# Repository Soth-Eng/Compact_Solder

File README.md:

# Compact_Solder
JBC Compact Soldering Station

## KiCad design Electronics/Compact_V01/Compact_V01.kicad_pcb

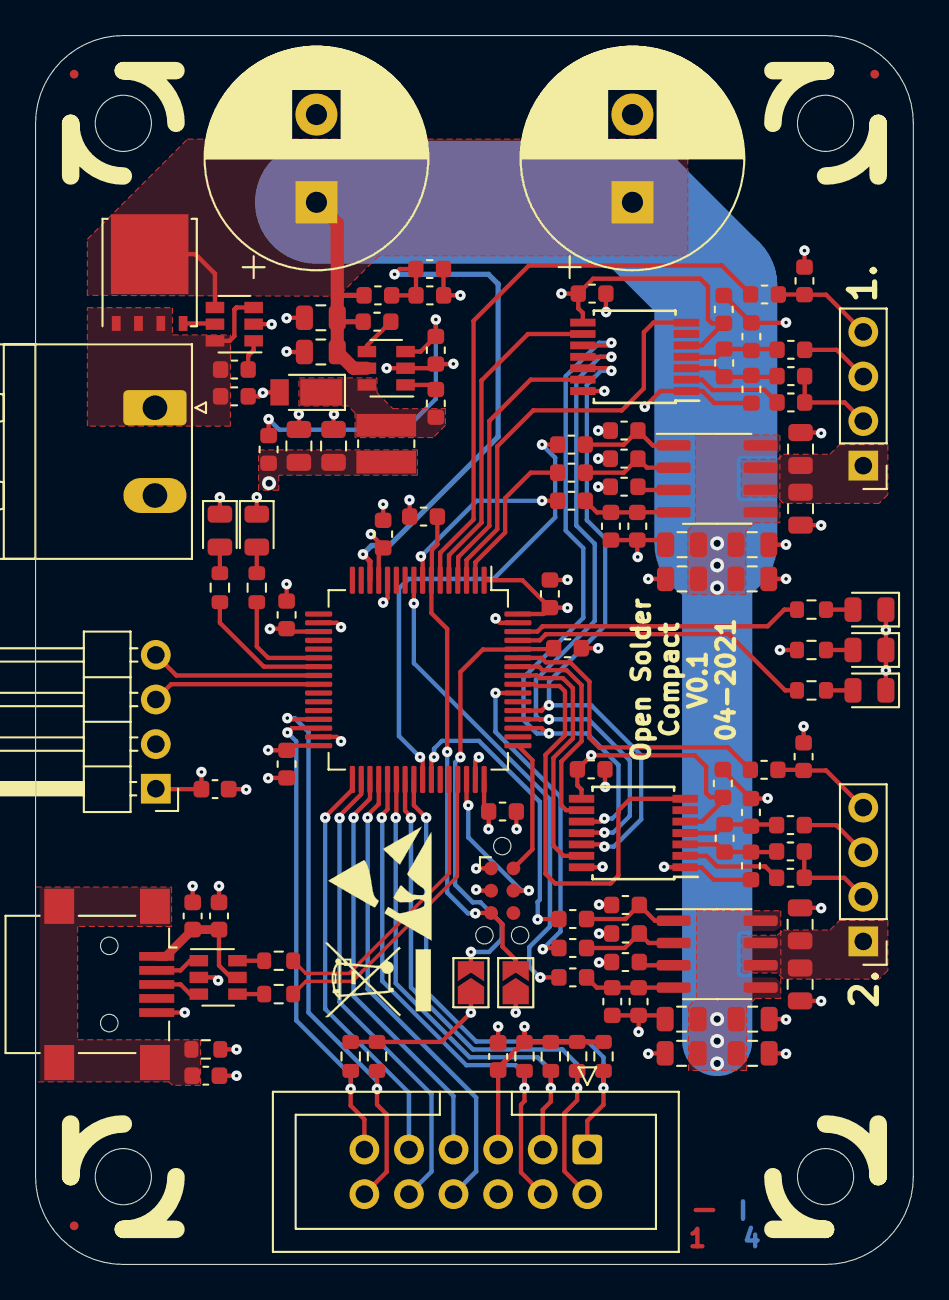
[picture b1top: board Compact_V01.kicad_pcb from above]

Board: 4 copper layers, 50.0 x 70.0 mm, 121 parts (0 on the bottom side), 81 nets.

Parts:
C1, C2, C3, C4, C13, C16, C20, C22, C23, C24, C31: 10nF; C_0603_1608Metric
C5, C6, C19, C21, C33, C34, C35, C56, C59, C60, C61, C62, C63, C64: 100nF; C_0603_1608Metric
C7, C8, C9, C10, C11, C12, C14, C15, C25, C26, C27, C28, C29, C30: 2.2uF; C_0805_2012Metric
C17, C18: 4.7uF; C_0805_2012Metric
C32: 1U; C_0603_1608Metric
C55: 22nF; C_0603_1608Metric
C57, C58: 1000uF; CP_Radial_D12.5mm_P5.00mm
D1: DFLS; D_PowerDI-123
D2, D3: GRN; LED_0805_2012Metric
D4: RED; LED_0805_2012Metric
D5, D6: BLUE; LED_0805_2012Metric
FID1, FID2, FID3: Fiducial; Fiducial_0.5mm_Mask1mm
H1, H2, H3, H4: MountingHole; MountingHole_3.2mm_M3_DIN965
J1, J2: IRON; PinHeader_1x04_P2.54mm_Vertical
J3: USB_B_Mini; USB_Mini-B_Lumberg_2486_01_Horizontal
J4: HMI; IDC-Header_2x06_P2.54mm_Vertical
J5: Power; PhoenixContact_MSTBA_2,5_2-G_1x02_P5.00mm_Horizontal
J6: PROG; Tag-Connect_TC2030-IDC-NL_2x03_P1.27mm_Vertical
J7: EXT; PinHeader_1x04_P2.54mm_Horizontal
JP1: RESET; SolderJumper-2_P1.3mm_Open_TrianglePad1.0x1.5mm
JP2: BOOT; SolderJumper-2_P1.3mm_Open_TrianglePad1.0x1.5mm
L1: 15uH; L_Wuerth_MAPI-3015
Q1: BSC028N06LS3; TDSON-8-1
R1, R7, R8, R17, R20, R27, R28: 10K; R_0603_1608Metric
R2: 1M; R_0603_1608Metric
R3, R4, R5, R23, R24, R25: 330E; R_0603_1608Metric
R6, R21: 22E; R_0603_1608Metric
R9, R10, R22, R26, R29, R30, R36, R37, R40, R41, R42, R43, R44: 1K; R_0603_1608Metric
R11, R31: 225E; R_0603_1608Metric
R12, R32: 0E; R_0603_1608Metric
R13, R14, R15, R33, R34, R35: 2K; R_0603_1608Metric
R16, R18: 100K; R_0603_1608Metric
R19: 33K; R_0603_1608Metric
R38, R39: 5.6K; R_0603_1608Metric
U1, U4: MAX31856; TSSOP-14_4.4x5mm_P0.65mm
U2, U5: NCV84140; SOIC-8_3.9x4.9mm_P1.27mm
U3: LMR16006YQ; SOT-23-6
U6: WE-TVS-82400102; SOT-23-6
U10: LM74700; SOT-23-6
U11: STM32L433RCTx; LQFP-64_10x10mm_P0.5mm

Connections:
+3V3: C5.1, C6.1, C17.1, C18.1, C19.1, C21.1, C34.1, C35.1, C60.1, C61.1, C62.1, C63.1, C64.1, J4.5, J6.1, J7.1, JP2.1, L1.2, R10.1, R19.1, R22.1, R26.1, R30.1, R36.1, R37.1, R38.1, R39.1, R40.1, U1.5, U1.8, U4.5, U4.8, U11.1, U11.13, U11.19, U11.32, U11.48, U11.64
+5V: C32.1, C33.1, J3.1, U6.5
/CS_1: R5.2, U11.8
/CS_2: R25.2, U11.9
/CS_EN_1: R4.2, U11.2
/CS_EN_2: R24.2, U11.55
/DRDY_1: U1.7, U11.3
/DRDY_2: U4.7, U11.56
/Detect_1: R9.2, U11.6
/Detect_2: R29.2, U11.59
/FAULT_1: U1.13, U11.4
/FAULT_2: U4.13, U11.57
/Front-End/HEATER: C7.1, C9.1, J1.1, U2.6, U2.7
/Front-End/Probe: J1.4, R9.1, R10.2
/Front-End/TC+: J1.3, R13.1
/MCU/BOOT0: JP2.2, R1.1, U11.60
/MCU/ERR: R42.1, U11.22
/MCU/H1_STAT: R43.1, U11.62
/MCU/H2_STAT: R44.1, U11.61
/MCU/I2C_SCL: J4.12, R39.2, U11.29
/MCU/I2C_SDA: J4.11, R38.2, U11.30
/MCU/IO_1: J4.1, R22.2, U11.40
/MCU/IO_2: J4.2, R26.2, U11.39
/MCU/IO_3: J4.3, R36.2, U11.38
/MCU/IO_4: J4.4, R37.2, U11.37
/MCU/NRST: C59.1, J6.5, JP1.2, U11.7
/MCU/RXD: J7.3, U11.25
/MCU/SPI_MISO: J4.7, U11.35
/MCU/SPI_MOSI: J4.8, U11.36
/MCU/SPI_NSS: J4.9, U11.33
/MCU/SPI_SCK: J4.10, U11.34
/MCU/STAT: R41.1, U11.23
/MCU/SWCLK: J6.2, U11.49
/MCU/SWDIO: J6.4, U11.46
/MCU/TXD: J7.4, U11.24
/MCU/USB_D+: R6.1, U11.45
/MCU/USB_D-: R21.1, U11.44
/PWM_IN_1: R3.2, U11.41
/PWM_IN_2: R23.2, U11.42
/SCK: U1.10, U4.10, U11.51
/SDI: U1.12, U4.12, U11.53
/SDO: U1.11, U4.11, U11.52
/SS_1: U1.9, U11.5
/SS_2: U4.9, U11.58
/VBUS_M: C13.1, R16.2, R17.1, U11.14
/sheet6064770F/HEATER: C25.1, C27.1, J2.1, U5.6, U5.7
/sheet6064770F/Probe: J2.4, R29.1, R30.2
/sheet6064770F/TC+: J2.3, R33.1
GND: C1.2, C2.1, C4.2, C5.2, C6.2, C7.2, C8.2, C9.2, C10.2, C11.2, C12.2, C13.2, C14.2, C15.2, C17.2, C18.2, C19.2, C20.2, C21.2, C22.1, C24.2, C25.2, C26.2, C27.2, C28.2, C29.2, C30.2, C31.2, C32.2, C33.2, C34.2, C35.2, C55.2, C57.2, C58.2, C59.2, C60.2, C61.2, C62.2, C63.2, C64.2, D1.2, D2.1, D3.1, D4.1, D5.1, D6.1, J1.2, J2.2, J3.5, J4.6, J5.2, J6.3, J7.2, JP1.1, R1.2, R2.2, R7.2, R8.2, R11.2, R12.2, R14.1, R15.1, R17.2, R20.2, R27.2, R28.2, R31.2, R32.2, R34.1, R35.1, U1.1, U1.14, U3.2, U4.1, U4.14, U6.2, U10.2, U11.12, U11.18, U11.31, U11.47, U11.63
unnamed: C1.1, R5.1, R11.1, U2.4
unnamed: C2.2, C3.1, R13.2, U1.4
unnamed: C3.2, C4.1, R14.2, U1.3
unnamed: C16.1, U3.1
unnamed: C16.2, D1.1, L1.1, U3.6
unnamed: C20.1, R25.1, R31.1, U5.4
unnamed: C22.2, C23.1, R33.2, U4.4
unnamed: C23.2, C24.1, R34.2, U4.3
unnamed: C31.1, J3.6, R2.1
unnamed: C55.1, C56.1, J5.1, Q1.1, Q1.2, Q1.3, U10.3, U10.6
unnamed: C56.2, U10.1
unnamed: D2.2, R40.2
unnamed: D3.2, R41.2
unnamed: D4.2, R42.2
unnamed: D5.2, R43.2
unnamed: D6.2, R44.2
unnamed: J3.2, U6.1
unnamed: J3.3, U6.3
unnamed: Q1.4, U10.5
unnamed: R3.1, R7.1, U2.1
unnamed: R4.1, R8.1, U2.2
unnamed: R6.2, U6.4
unnamed: R12.1, U2.3
unnamed: R15.2, U1.2
unnamed: R18.2, U3.4
unnamed: R19.2, R20.1, U3.3
unnamed: R21.2, U6.6
unnamed: R23.1, R27.1, U5.1
unnamed: R24.1, R28.1, U5.2
unnamed: R32.1, U5.3
unnamed: R35.2, U4.2
VBUS: C8.1, C10.1, C11.1, C12.1, C14.1, C15.1, C26.1, C28.1, C29.1, C30.1, C57.1, C58.1, Q1.5, R16.1, R18.1, U2.5, U2.8, U3.5, U5.5, U5.8, U10.4

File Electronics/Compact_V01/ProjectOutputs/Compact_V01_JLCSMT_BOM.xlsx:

Comment | Designator | Footprint
WEEE-Logo_4.2x6mm_SilkScreen | REF** | WEEE-Logo_4.2x6mm_SilkScreen
ESD-Logo_6.6x6mm_SilkScreen | REF** | ESD-Logo_6.6x6mm_SilkScreen
1K | R44,R43,R42,R41,R40,R37,R36,R26,R22,R30,R29,R10,R9 | R_0603_1608Metric
BLUE | D6,D5 | LED_0805_2012Metric
RED | D4 | LED_0805_2012Metric
GRN | D3,D2 | LED_0805_2012Metric
EXT | J7 | PinHeader_1x04_P2.54mm_Horizontal
100nF | C35,C34,C33,C64,C63,C62,C61,C60,C59,C56,C21,C19,C6,C5 | C_0603_1608Metric
BOOT | JP2 | SolderJumper-2_P1.3mm_Open_TrianglePad1.0x1.5mm
RESET | JP1 | SolderJumper-2_P1.3mm_Open_TrianglePad1.0x1.5mm
PROG | J6 | Tag-Connect_TC2030-IDC-NL_2x03_P1.27mm_Vertical
5.6K | R39,R38 | R_0603_1608Metric
HMI | J4 | IDC-Header_2x06_P2.54mm_Vertical
WE-TVS-82400102 | U6 | SOT-23-6
22E | R21,R6 | R_0603_1608Metric
1M | R2 | R_0603_1608Metric
1U | C32 | C_0603_1608Metric
10nF | C31,C24,C23,C22,C20,C16,C13,C4,C3,C2,C1 | C_0603_1608Metric
USB_B_Mini | J3 | USB_Mini-B_Lumberg_2486_01_Horizontal
IRON | J2,J1 | PinHeader_1x04_P2.54mm_Vertical
Power | J5 | PhoenixContact_MSTBA_2,5_2-G_1x02_P5.00mm_Horizontal
STM32L433RCTx | U11 | LQFP-64_10x10mm_P0.5mm
10K | R1,R28,R27,R20,R17,R8,R7 | R_0603_1608Metric
1000uF | C58,C57 | CP_Radial_D12.5mm_P5.00mm
LM74700 | U10 | SOT-23-6
BSC028N06LS3 | Q1 | TDSON-8-1
22nF | C55 | C_0603_1608Metric
NCV84140 | U5,U2 | SOIC-8_3.9x4.9mm_P1.27mm
MAX31856 | U4,U1 | TSSOP-14_4.4x5mm_P0.65mm
2K | R35,R34,R33,R15,R14,R13 | R_0603_1608Metric
0E | R32,R12 | R_0603_1608Metric
225E | R31,R11 | R_0603_1608Metric
330E | R25,R24,R23,R5,R4,R3 | R_0603_1608Metric
2.2uF | C30,C29,C28,C27,C26,C25,C15,C14,C12,C11,C10,C9,C8,C7 | C_0805_2012Metric
MountingHole | H4,H3,H2,H1 | MountingHole_3.2mm_M3_DIN965
Fiducial | FID3,FID2,FID1 | Fiducial_0.5mm_Mask1mm
LMR16006YQ | U3 | SOT-23-6
33K | R19 | R_0603_1608Metric
100K | R18,R16 | R_0603_1608Metric
15uH | L1 | L_Wuerth_MAPI-3015
DFLS | D1 | D_PowerDI-123
4.7uF | C18,C17 | C_0805_2012Metric
